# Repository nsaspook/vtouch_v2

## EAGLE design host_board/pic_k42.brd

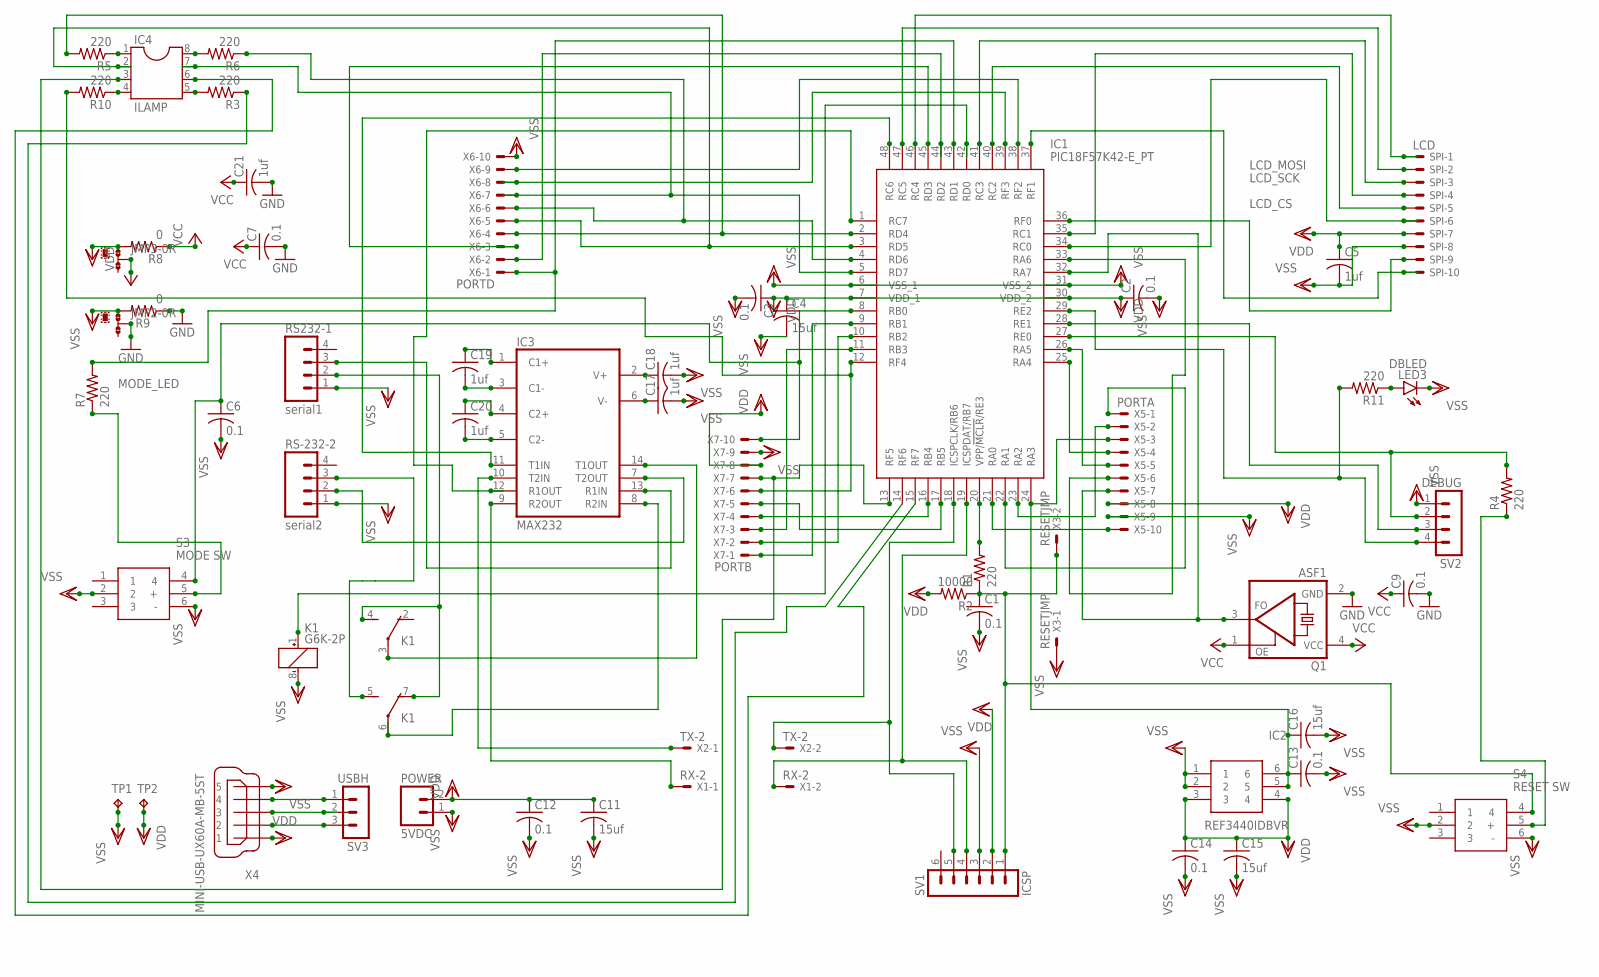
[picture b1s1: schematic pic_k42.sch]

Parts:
C1, C2, C3, C6, C7, C9, C12, C13, C14: 0.1; C1206
C4, C11, C15, C16: 15uf; C1206
C5, C17, C18, C19, C20, C21: 1uf; C0805
IC1: PIC18F57K42-E_PT; QFP50P900X900X120-48N
IC2: REF3440IDBVR; SOP95P280X145-6N
IC3: MAX232; DIL16
IC4: ILAMP; SOCKET-08
JMP2, JMP3: 0R-JUMPA; A0R-JMP
K1: G6K-2P
LED3: DBLED; CHIPLED_1206
POWER: 5VDC; 02P
Q1: ASF1; ASF
R1, R3, R4, R5, R6, R7, R10, R11: 220; R1206
R2: 10000; R1206
R8, R9: 0; R1206
RS232-1: serial1; 04P
RS-232-2: serial2; 04P
S3: MODE SW; B3W-9_1-LED
S4: RESET SW; B3W-9_1-LED
SPI: LCD; 22-23-2101
SV1: ICSP; MA06-1
SV2: DEBUG; MA04-1
SV3: USBH; MA03-1
TP1, TP2: TPB1,27; B1,27
X1: RX-2; 332-02
X2: TX-2; 332-02
X3: RESETJMP; 332-02
X4: MINI-USB-UX60A-MB-5ST; UX60A-MB-5ST
X5: PORTA; 22-23-2101
X6: PORTD; 22-23-2101
X7: PORTB; 22-23-2101

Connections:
GND: C7.2, C9.2, C21.2, IC3.15 (GND), JMP2.2, Q1.2 (GND), R9.1
LCD_CS: IC1.40 (RC2), SPI.5
LCD_MOSI: IC1.47 (RC5), SPI.2
LCD_SCK: IC1.41 (RC3), SPI.3
MODE_LED: IC1.43 (RD1), R7.2, X6.1
unnamed: C1.1, R1.1, R2.1, S4.4, SV1.1, X3.2
unnamed: IC1.20 (VPP/!MCLR!/RE3), R1.2
unnamed: IC4.1, R5.1
unnamed: IC1.32 (RA7), Q1.3 (FO), X5.7
unnamed: C17.1, IC3.6 (V-)
unnamed: IC1.19 (ICSPDAT/RB7), SV1.4, X1.2
unnamed: IC1.18 (ICSPCLK/RB6), SV1.5, X2.2
unnamed: C13.1, C16.1, IC1.24 (RA3), IC2.5, IC2.6, X5.3
unnamed: C18.1, IC3.2 (V+)
unnamed: C19.1, IC3.1 (C1+)
unnamed: C20.1, IC3.4 (C2+)
unnamed: C20.2, IC3.5 (C2-)
unnamed: C19.2, IC3.3 (C1-)
unnamed: K1.4 (S), K1.7 (O), RS232-1.2
unnamed: IC3.7 (T2OUT), RS-232-2.2
unnamed: IC3.13 (R1IN), RS232-1.3
unnamed: IC4.8, R6.2
unnamed: IC1.1 (RC7), IC3.12 (R1OUT)
unnamed: IC3.9 (R2OUT), X1.1
unnamed: IC1.48 (RC6), IC3.11 (T1IN)
unnamed: R4.1, S4.5 (+)
unnamed: IC3.10 (T2IN), X2.1
unnamed: IC1.27 (RE0), R4.2, SV2.2
unnamed: IC1.28 (RE1), SV2.3
unnamed: IC1.29 (RE2), R11.2, SV2.4
unnamed: IC3.14 (T1OUT), K1.3
unnamed: IC3.8 (R2IN), K1.6
unnamed: IC1.42 (RD0), K1.1 (+)
unnamed: IC1.46 (RC4), SPI.1
unnamed: IC1.35 (RC1), SPI.4
unnamed: IC1.34 (RC0), SPI.6
unnamed: IC1.26 (RA5), X5.5
unnamed: IC1.25 (RA4), X5.4
unnamed: IC1.23 (RA2), X5.2
unnamed: IC1.22 (RA1), X5.1
unnamed: IC1.21 (RA0), X5.10
unnamed: IC1.33 (RA6), X5.6
unnamed: IC1.36 (RF0), SPI.9
unnamed: IC1.37 (RF1), SPI.10
unnamed: C6.1, IC1.8 (RB0), S3.4, X7.10
unnamed: IC1.44 (RD2), X6.2
unnamed: IC1.45 (RD3), X6.3
unnamed: IC1.2 (RD4), R5.2, X6.4
unnamed: IC1.3 (RD5), IC4.2, X6.5
unnamed: IC1.4 (RD6), R6.1, X6.6
unnamed: IC1.5 (RD7), IC4.7, X6.7
unnamed: IC1.38 (RF2), X6.9
unnamed: IC1.39 (RF3), X6.8
unnamed: IC1.9 (RB1), X7.1
unnamed: IC1.10 (RB2), X7.2
unnamed: IC4.5, R3.2
unnamed: IC1.16 (RB4), X7.4
unnamed: IC1.17 (RB5), X7.5
unnamed: IC1.12 (RF4), R10.2, X7.6
unnamed: IC1.13 (RF5), IC4.3, X7.7
unnamed: IC1.15 (RF7), IC4.6
unnamed: IC1.14 (RF6), R3.1
unnamed: K1.5 (S), RS-232-2.3
unnamed: IC4.4, R10.1
unnamed: R7.1, S3.5 (+)
unnamed: LED3.A, R11.1
unnamed: IC1.11 (RB3), X7.3
unnamed: SV3.1, X4.4
unnamed: SV3.2, X4.3
unnamed: SV3.3, X4.2
VCC: C7.1, C9.1, C21.1, IC3.16 (VCC), JMP3.2, Q1.1 (OE), Q1.4 (VCC), R8.1
VDD: C2.1, C3.1, C4.1, C5.1, C11.1, C12.1, C14.1, C15.1, IC1.7 (VDD_1), IC1.30 (VDD_2), IC2.3, IC2.4, JMP3.1, POWER.2, R2.2, R8.2, SPI.7, SV1.2, TP2.TP, X4.1, X5.8, X7.8
VSS: C1.2, C2.2, C3.2, C4.2, C5.2, C6.2, C11.2, C12.2, C13.2, C14.2, C15.2, C16.2, C17.2, C18.2, IC1.6 (VSS_1), IC1.31 (VSS_2), IC2.1, IC2.2, JMP2.1, K1.8 (-), LED3.C, POWER.1, R9.2, RS232-1.1, RS-232-2.1, S3.2, S3.6 (-), S4.2, S4.6 (-), SPI.8, SV1.3, SV2.1, TP1.TP, X3.1, X4.5, X5.9, X6.10, X7.9

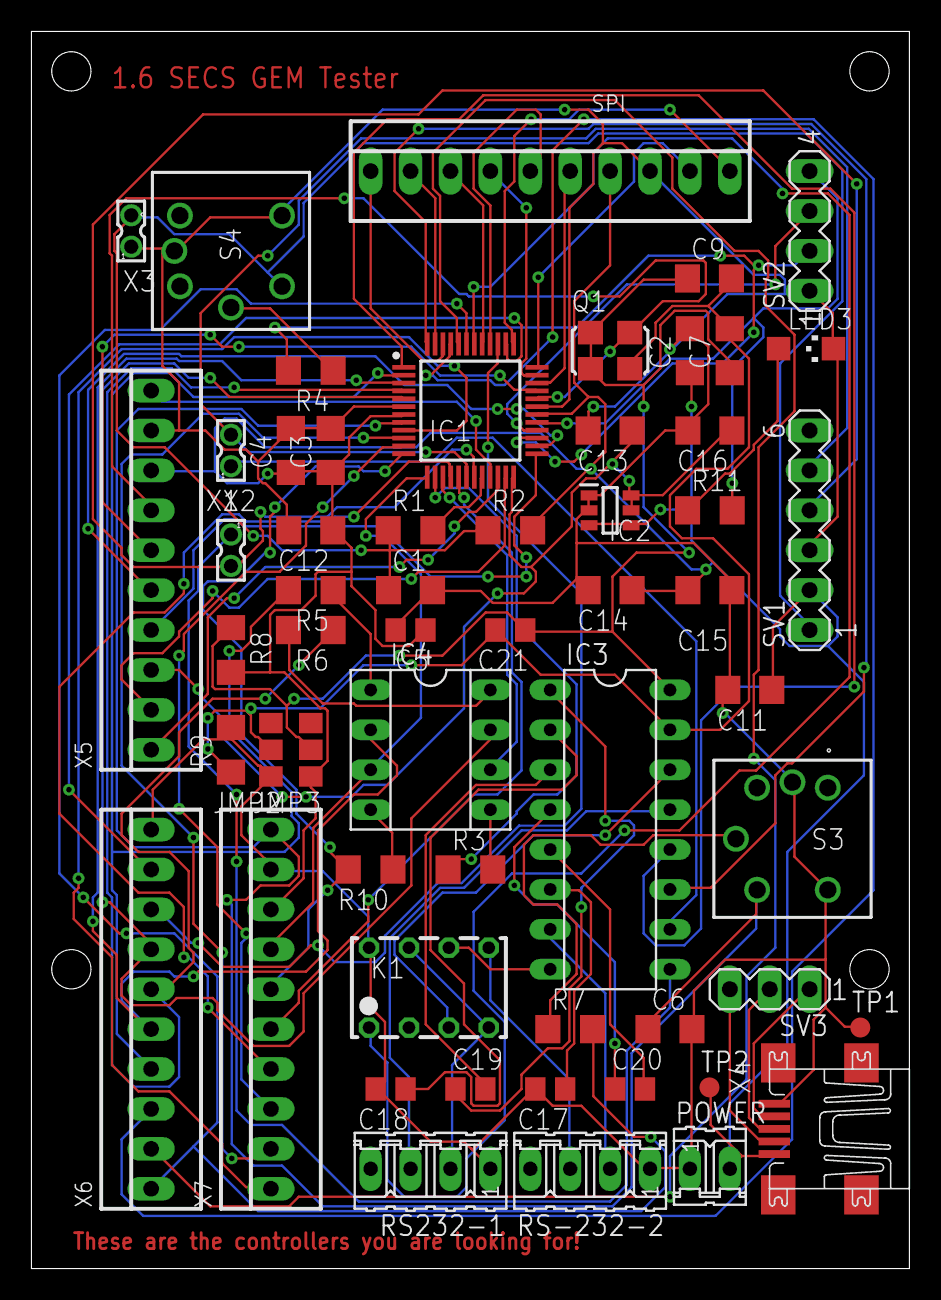
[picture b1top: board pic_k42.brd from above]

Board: 2 copper layers, 55.9 x 78.7 mm, 57 parts (0 on the bottom side), 73 nets.

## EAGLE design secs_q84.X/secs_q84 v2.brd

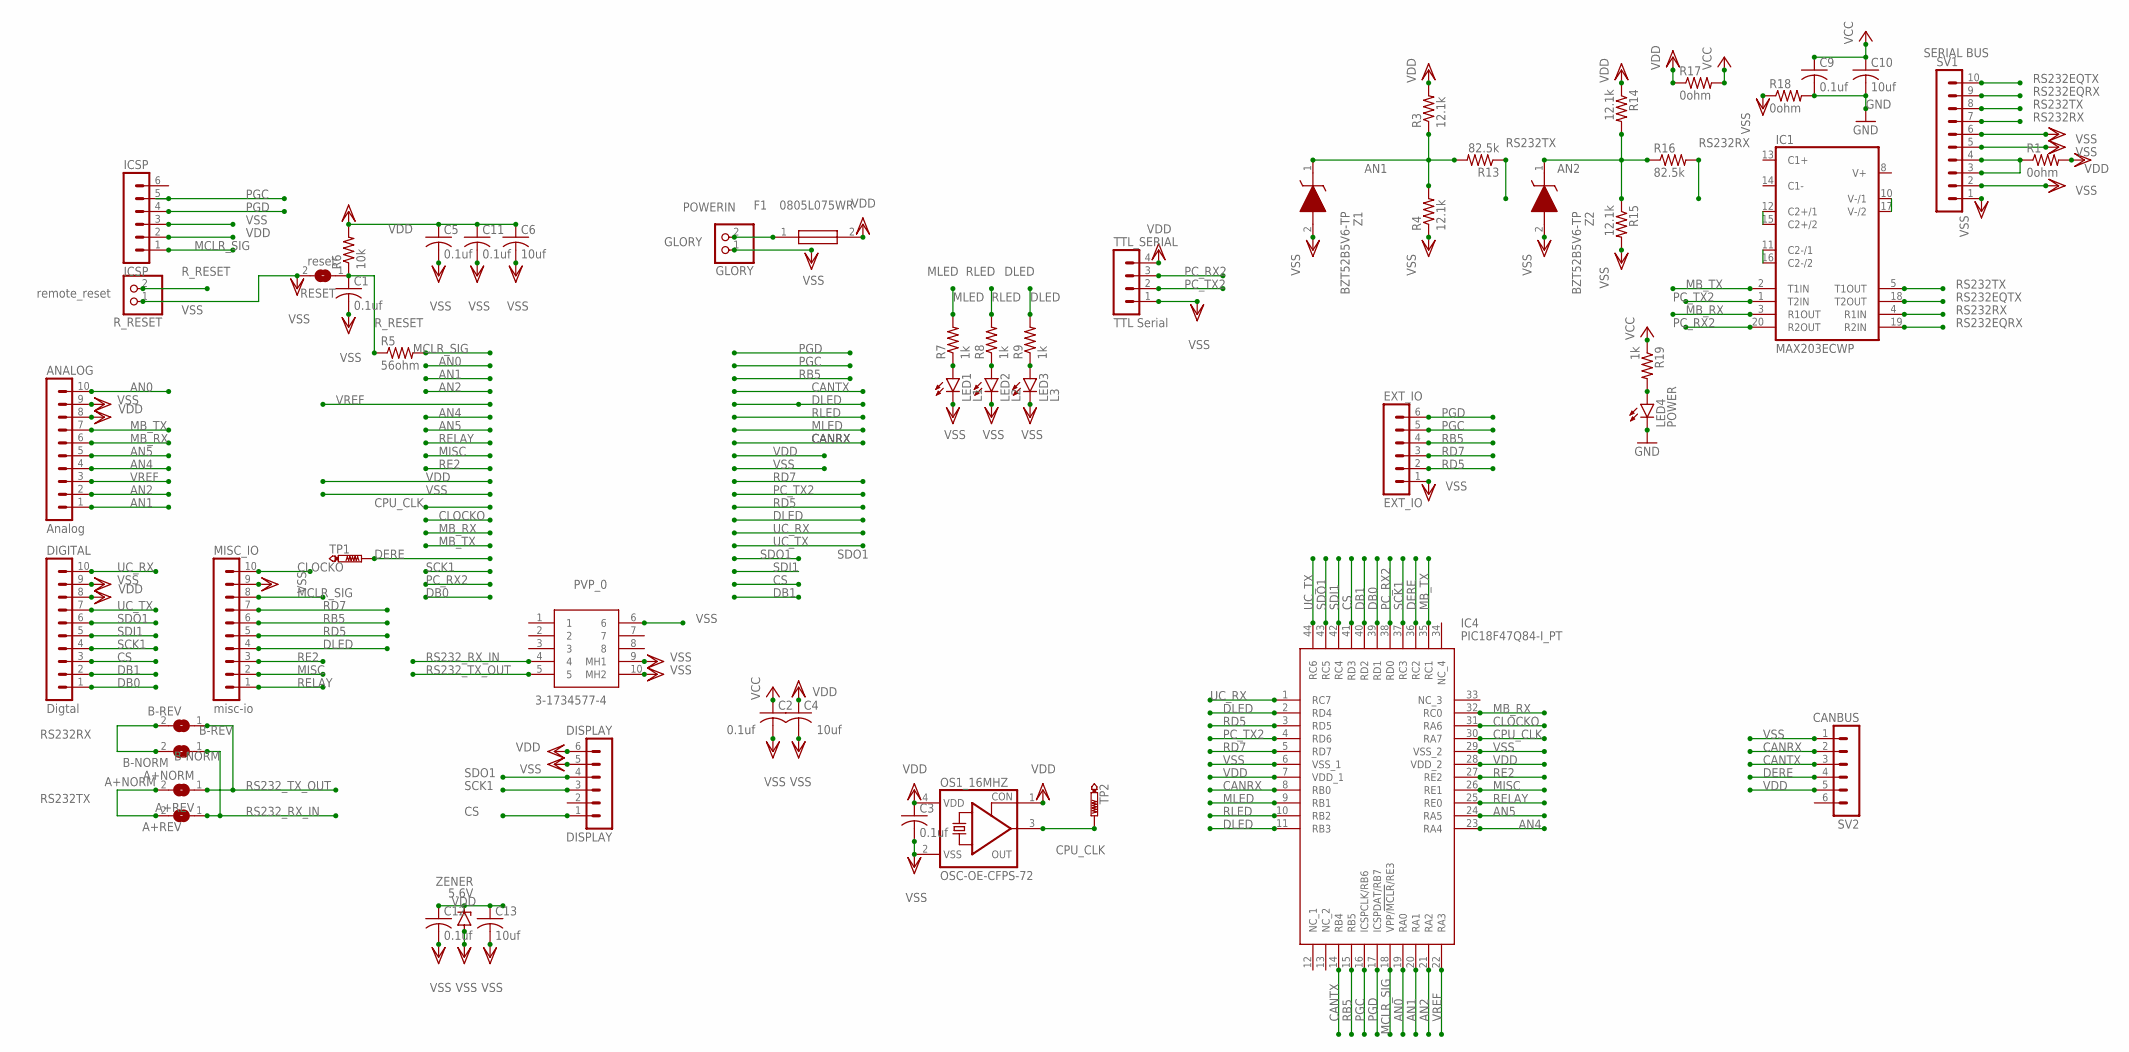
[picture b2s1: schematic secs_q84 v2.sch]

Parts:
A+NORM: A+NORM; SJ
A+REV: A+REV; SJ
ANALOG: Analog; MA10-1
B-NORM: B-NORM; SJ
B-REV: B-REV; SJ
C1, C2, C3, C5, C9, C11, C12: 0.1uf; C0805
C4, C6, C10, C13: 10uf; C0805
DIGITAL: Digtal; MA10-1
DISPLAY: DISPLAY; MA06-1
EXT_IO: EXT_IO; MA06-1
F1: 0805L075WR; FUSC2114X125N
GLORY: GLORY; 1X02
IC1: MAX203ECWP; SO20L
IC4: PIC18F47Q84-I_PT; QFP80P1200X1200X120-44N
ICSP: ICSP; MA06-1
LED1: L1; CHIPLED_0805
LED2: L2; CHIPLED_0805
LED3: L3; CHIPLED_0805
LED4: POWER; CHIP-LED0603
MISC_IO: misc-io; MA10-1
OS1_16MHZ: OSC-OE-CFPS-72; 7.2X5.2-4-PAD
PVP_0: 3-1734577-4; 317345774
R1, R17, R18: 0ohm; R0805
R3, R4, R14, R15: 12.1k; R0805
R5: 56ohm; R0805
R6: 10k; R0805
R7, R8, R9, R19: 1k; R0805
R13, R16: 82.5k; R0805
RESET: reset; SJ
R_RESET: remote_reset; 1X02
SV1: SERIAL BUS; MA10-1
SV2: CANBUS; MA06-1
TP1, TP2: PTR1PAD1-13; P1-13
TTL_SERIAL: TTL Serial; MA04-1
Z1, Z2: BZT52B5V6-TP; SOD3716X135N
ZENER: 5.6V; SMB

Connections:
AN0: ANALOG.10, IC4.19 (RA0)
AN1: ANALOG.1, IC4.20 (RA1), R3.1, R4.2, R13.2, Z1.1 (K)
AN2: ANALOG.2, IC4.21 (RA2), R14.2, R15.1, R16.1, Z2.1 (K)
AN4: ANALOG.4, IC4.23 (RA4)
AN5: ANALOG.5, IC4.24 (RA5)
CANRX: IC4.8 (RB0), SV2.2
CANTX: IC4.14 (RB4), SV2.3
CLOCKO: IC4.31 (RA6), MISC_IO.10
CPU_CLK: IC4.30 (RA7), OS1_16MHZ.3 (OUT), TP2.TP
CS: DIGITAL.3, DISPLAY.1, IC4.41 (RD3)
DB0: DIGITAL.1, IC4.39 (RD1)
DB1: DIGITAL.2, IC4.40 (RD2)
DERE: IC4.36 (RC2), SV2.4, TP1.TP
DLED: IC4.2 (RD4), IC4.11 (RB3), MISC_IO.4, R9.2
DPOWER: R1.1, SV1.3, SV1.4
GND: C9.2, C10.2, IC1.6 (GND), IC1.9 (GND), LED4.C, R18.2
MB_RX: ANALOG.6, IC1.3 (R1OUT), IC4.32 (RC0)
MB_TX: ANALOG.7, IC1.2 (T1IN), IC4.35 (RC1)
MCLR_SIG: IC4.18 (VPP/!MCLR!/RE3), ICSP.1, MISC_IO.8, R5.2
MISC: IC4.26 (RE1), MISC_IO.2
MLED: IC4.9 (RB1), R7.2
unnamed: IC1.10 (V-/1), IC1.17 (V-/2)
unnamed: IC1.12 (C2+/1), IC1.15 (C2+/2)
unnamed: LED4.A, R19.2
unnamed: LED1.A, R7.1
unnamed: LED2.A, R8.1
unnamed: LED3.A, R9.1
unnamed: IC1.11 (C2-/1), IC1.16 (C2-/2)
PC_RX2: IC1.20 (R2OUT), IC4.38 (RD0), TTL_SERIAL.3
PC_TX2: IC1.1 (T2IN), IC4.4 (RD6), TTL_SERIAL.2
PGC: EXT_IO.5, IC4.16 (ICSPCLK/RB6), ICSP.5
PGD: EXT_IO.6, IC4.17 (ICSPDAT/RB7), ICSP.4
POWERIN: F1.1, GLORY.2
RB5: EXT_IO.4, IC4.15 (RB5), MISC_IO.6
RD5: EXT_IO.2, IC4.3 (RD5), MISC_IO.5
RD7: EXT_IO.3, IC4.5 (RD7), MISC_IO.7
RE2: IC4.27 (RE2), MISC_IO.3
RELAY: IC4.25 (RE0), MISC_IO.1
RLED: IC4.10 (RB2), R8.2
RS232EQRX: IC1.19 (R2IN), SV1.9
RS232EQTX: IC1.18 (T2OUT), SV1.10
RS232RX: B-NORM.2, B-REV.2, IC1.4 (R1IN), R16.2, SV1.7
RS232TX: A+NORM.2, A+REV.2, IC1.5 (T1OUT), R13.1, SV1.8
RS232_RX_IN: A+REV.1, B-NORM.1, PVP_0.4
RS232_TX_OUT: A+NORM.1, B-REV.1, PVP_0.5
R_RESET: C1.1, R5.1, R6.1, RESET.1, R_RESET.2
SCK1: DIGITAL.4, DISPLAY.3, IC4.37 (RC3)
SDI1: DIGITAL.5, IC4.42 (RC4)
SDO1: DIGITAL.6, DISPLAY.4, IC4.43 (RC5)
UC_RX: DIGITAL.10, IC4.1 (RC7)
UC_TX: DIGITAL.7, IC4.44 (RC6)
VCC: C2.1, C9.1, C10.1, IC1.7 (VCC), R17.2, R19.1
VDD: ANALOG.8, C3.1, C4.1, C5.1, C6.1, C11.1, C12.1, C13.1, DIGITAL.8, DISPLAY.6, F1.2, IC4.7 (VDD_1), IC4.28 (VDD_2), ICSP.2, OS1_16MHZ.1 (CON), OS1_16MHZ.4 (VDD), R1.2, R3.2, R6.2, R14.1, R17.1, SV2.5, TTL_SERIAL.4, ZENER.C
VREF: ANALOG.3, IC4.22 (RA3)
VSS: ANALOG.9, C1.2, C2.2, C3.2, C4.2, C5.2, C6.2, C11.2, C12.2, C13.2, DIGITAL.9, DISPLAY.5, EXT_IO.1, GLORY.1, IC4.6 (VSS_1), IC4.29 (VSS_2), ICSP.3, LED1.C, LED2.C, LED3.C, MISC_IO.9, OS1_16MHZ.2 (VSS), PVP_0.6, PVP_0.9 (MH1), PVP_0.10 (MH2), R4.1, R15.2, R18.1, RESET.2, R_RESET.1, SV1.1, SV1.2, SV1.5, SV1.6, SV2.1, TTL_SERIAL.1, Z1.2 (A), Z2.2 (A), ZENER.A

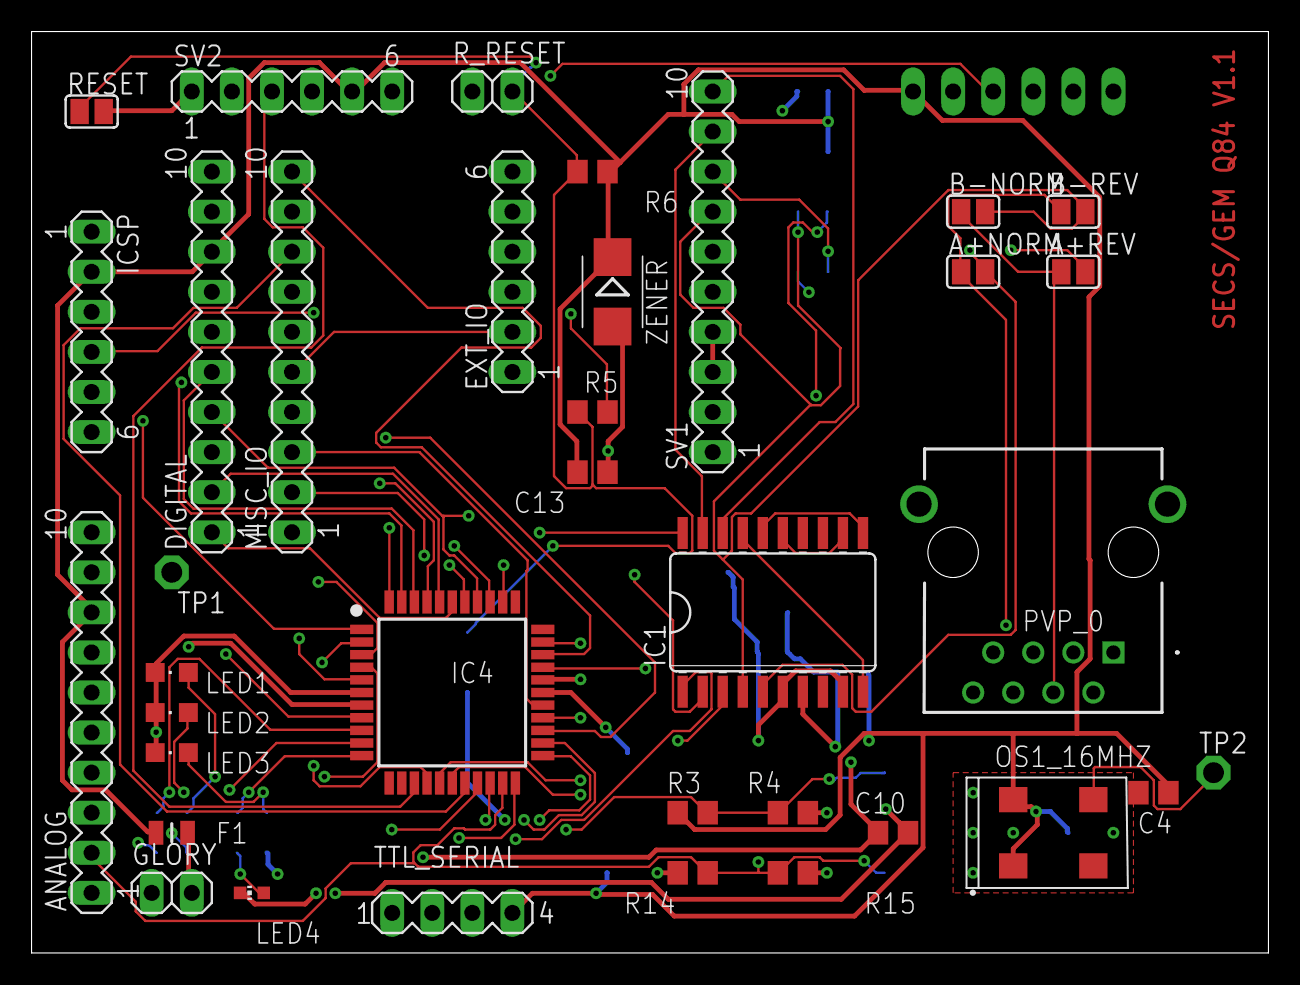
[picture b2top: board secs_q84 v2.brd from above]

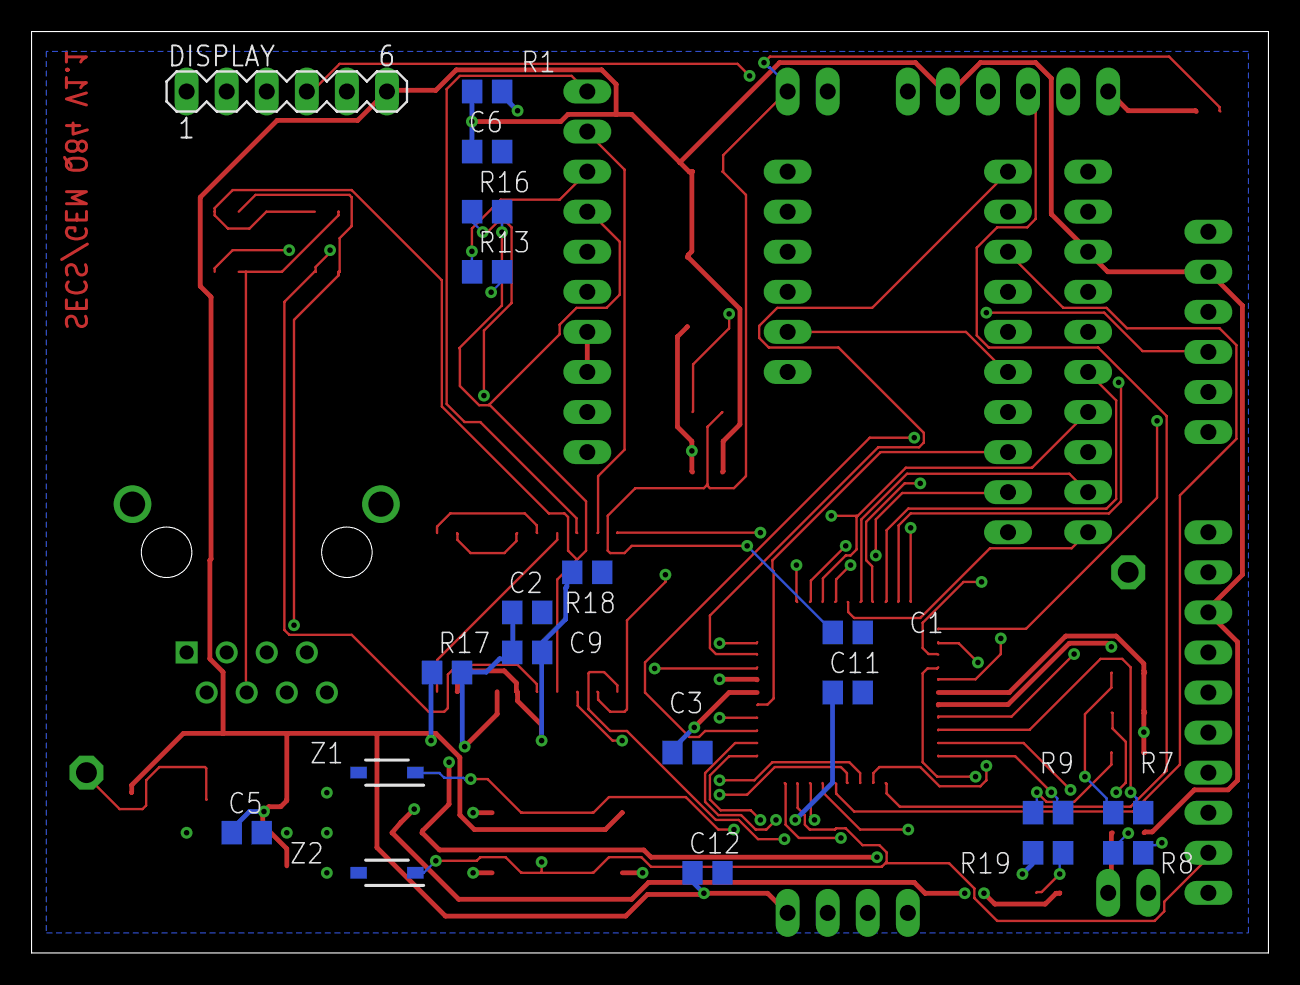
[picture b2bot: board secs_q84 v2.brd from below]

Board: 4 copper layers, 78.4 x 58.4 mm, 56 parts (20 on the bottom side), 55 nets.

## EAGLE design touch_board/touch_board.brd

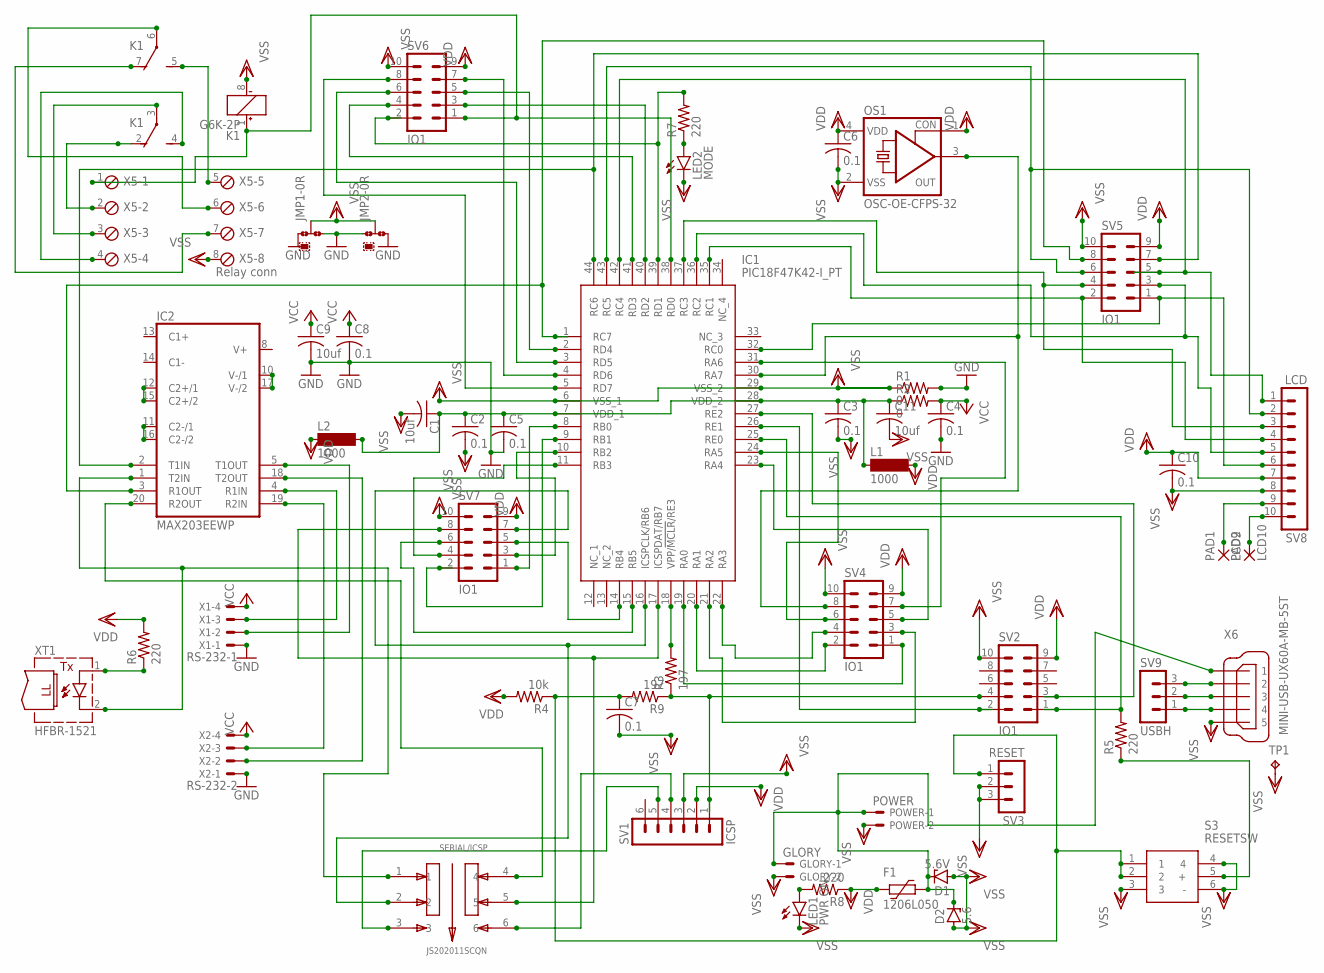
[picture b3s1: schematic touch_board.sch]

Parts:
C1, C9, C11: 10uf; C0805
C2, C3, C4, C5, C6, C7, C8, C10: 0.1; C0805
D1: 5.6V; ZDIO-7.5
D2: 5.6; SMB
F1: 1206L050; 1206L
GLORY: GLORY; 22-23-2021
IC1: PIC18F47K42-I_PT; QFP80P1200X1200X120-44N
IC2: MAX203EEWP; SO20L
JMP1, JMP2: 0R-JUMPA; A0R-JMP
K1: G6K-2P
L1, L2: 1000; SM-1206
LED1: PWR ON; CHIPLED_1206
LED2: MODE; CHIPLED_1206
OS1: OSC-OE-CFPS-32; 7.2X5.2-4-PAD
PAD1: LCD9; SMD1,27-2,54
PAD2: LCD10; SMD1,27-2,54
POWER: POWER; 22-23-2021
R1, R2: 0; R0805
R3, R9: 197; R0805
R4: 10k; R0805
R5, R6, R7, R8: 220; R0805
S3: RESETSW; B3W-9_1-LED
SERIAL/ICSP: JS202011SCQN; SW_JS202011SCQN
SV1: ICSP; MA06-1
SV2, SV4, SV5, SV6, SV7: IO1; MA05-2
SV3: RESET; MA03-1
SV8: LCD; MA10-1
SV9: USBH; MA03-1
TP1: TPB1,27; B1,27
X1: RS-232-1; 22-23-2041
X2: RS-232-2; 22-23-2041
X5: Relay conn; 8POL254
X6: MINI-USB-UX60A-MB-5ST; UX60A-MB-5ST
XT1: HFBR-1521; HFBR-15X3

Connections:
GND: C4.2, C5.2, C8.2, C9.2, IC2.6 (GND), IC2.9 (GND), JMP1.1, JMP1.3, JMP2.1, JMP2.3, R1.2, X1.1, X2.1
unnamed: IC1.30 (RA7), OS1.3 (OUT), SV4.8
unnamed: R3.1, R9.1, SV1.1, SV2.4
unnamed: IC1.18 (VPP/!MCLR!/RE3), R3.2
unnamed: IC1.25 (RE0), R5.2, SV2.1
unnamed: IC1.26 (RE1), SV2.2
unnamed: IC1.17 (ICSPDAT/RB7), SERIAL/ICSP.5, SV7.8
unnamed: IC1.16 (ICSPCLK/RB6), SERIAL/ICSP.2, SV7.7
unnamed: IC1.27 (RE2), SV2.3
unnamed: R5.1, S3.5 (+)
unnamed: IC1.39 (RD1), R7.2, SV6.2
unnamed: LED2.A, R7.1
unnamed: IC2.11 (C2-/1), IC2.16 (C2-/2)
unnamed: IC2.10 (V-/1), IC2.17 (V-/2)
unnamed: IC2.12 (C2+/1), IC2.15 (C2+/2)
unnamed: IC2.5 (T1OUT), X1.2
unnamed: IC2.18 (T2OUT), X2.2
unnamed: IC2.4 (R1IN), X1.3
unnamed: IC2.19 (R2IN), X2.3
unnamed: IC1.44 (RC6), IC2.2 (T1IN), SV5.7
unnamed: IC2.1 (T2IN), SERIAL/ICSP.1, XT1.2 (C)
unnamed: IC1.1 (RC7), IC2.3 (R1OUT), SV5.8
unnamed: IC2.20 (R2OUT), SERIAL/ICSP.4
unnamed: SERIAL/ICSP.6, SV1.4
unnamed: R6.1, XT1.1 (A)
unnamed: IC1.19 (RA0), SV4.1
unnamed: IC1.20 (RA1), SV4.2
unnamed: IC1.21 (RA2), SV4.3
unnamed: IC1.22 (RA3), SV4.4
unnamed: IC1.23 (RA4), SV4.5
unnamed: IC1.31 (RA6), SV4.7
unnamed: IC1.24 (RA5), SV4.6
unnamed: IC1.32 (RC0), SV5.1, SV8.6
unnamed: IC1.35 (RC1), SV5.2, SV8.4
unnamed: IC1.36 (RC2), SV5.3, SV8.5
unnamed: IC1.37 (RC3), SV5.4, SV8.3
unnamed: LED1.A, R8.2
unnamed: IC1.43 (RC5), SV5.6, SV8.2
unnamed: K1.2 (O), X5.2
unnamed: IC1.40 (RD2), SV6.3
unnamed: IC1.41 (RD3), SV6.4
unnamed: IC1.2 (RD4), SV6.5
unnamed: IC1.3 (RD5), SV6.6
unnamed: IC1.4 (RD6), SV6.7
unnamed: IC1.5 (RD7), SV6.8
unnamed: IC1.8 (RB0), SV7.1
unnamed: IC1.9 (RB1), SV7.2
unnamed: IC1.10 (RB2), SV7.3
unnamed: IC1.11 (RB3), SV7.4
unnamed: IC1.14 (RB4), SV7.5
unnamed: IC1.15 (RB5), SV7.6
unnamed: IC1.38 (RD0), K1.1 (+), SV6.1, X5.1
unnamed: K1.3, X5.3
unnamed: K1.4 (S), X5.4
unnamed: K1.5 (S), X5.5
unnamed: K1.6, X5.6
unnamed: K1.7 (O), X5.7
unnamed: C1.1, C2.1, C3.1, C5.1, C11.1, IC1.7 (VDD_1), IC1.28 (VDD_2), L1.1, L2.2, R2.1
unnamed: SV9.3, X6.2
unnamed: D1.C, D2.C, F1.1, GLORY.1, POWER.1, X6.1
unnamed: SV9.2, X6.3
unnamed: C7.1, R4.1, R9.2, S3.1, S3.2, SV3.1
unnamed: IC1.42 (RC4), SV5.5, SV8.1
unnamed: SV9.1, X6.4
unnamed: SERIAL/ICSP.3, SV1.5
unnamed: PAD1.1, SV8.9
unnamed: PAD2.1, SV8.10
VCC: C4.1, C8.1, C9.1, IC2.7 (VCC), R2.2, X1.4, X2.4
VDD: C6.1, C10.1, F1.2, L1.2, L2.1, OS1.1 (CON), OS1.4 (VDD), R4.2, R6.2, R8.1, SV1.2, SV2.9, SV4.9, SV5.9, SV6.9, SV7.9, SV8.7
VSS: C1.2, C2.2, C3.2, C6.2, C7.2, C10.2, C11.2, D1.A, D2.A, GLORY.2, IC1.6 (VSS_1), IC1.29 (VSS_2), JMP1.2, JMP2.2, K1.8 (-), LED1.C, LED2.C, OS1.2 (VSS), POWER.2, R1.1, S3.3, S3.4, S3.6 (-), SV1.3, SV2.10, SV3.2, SV3.3, SV4.10, SV5.10, SV6.10, SV7.10, SV8.8, TP1.TP, X5.8, X6.5

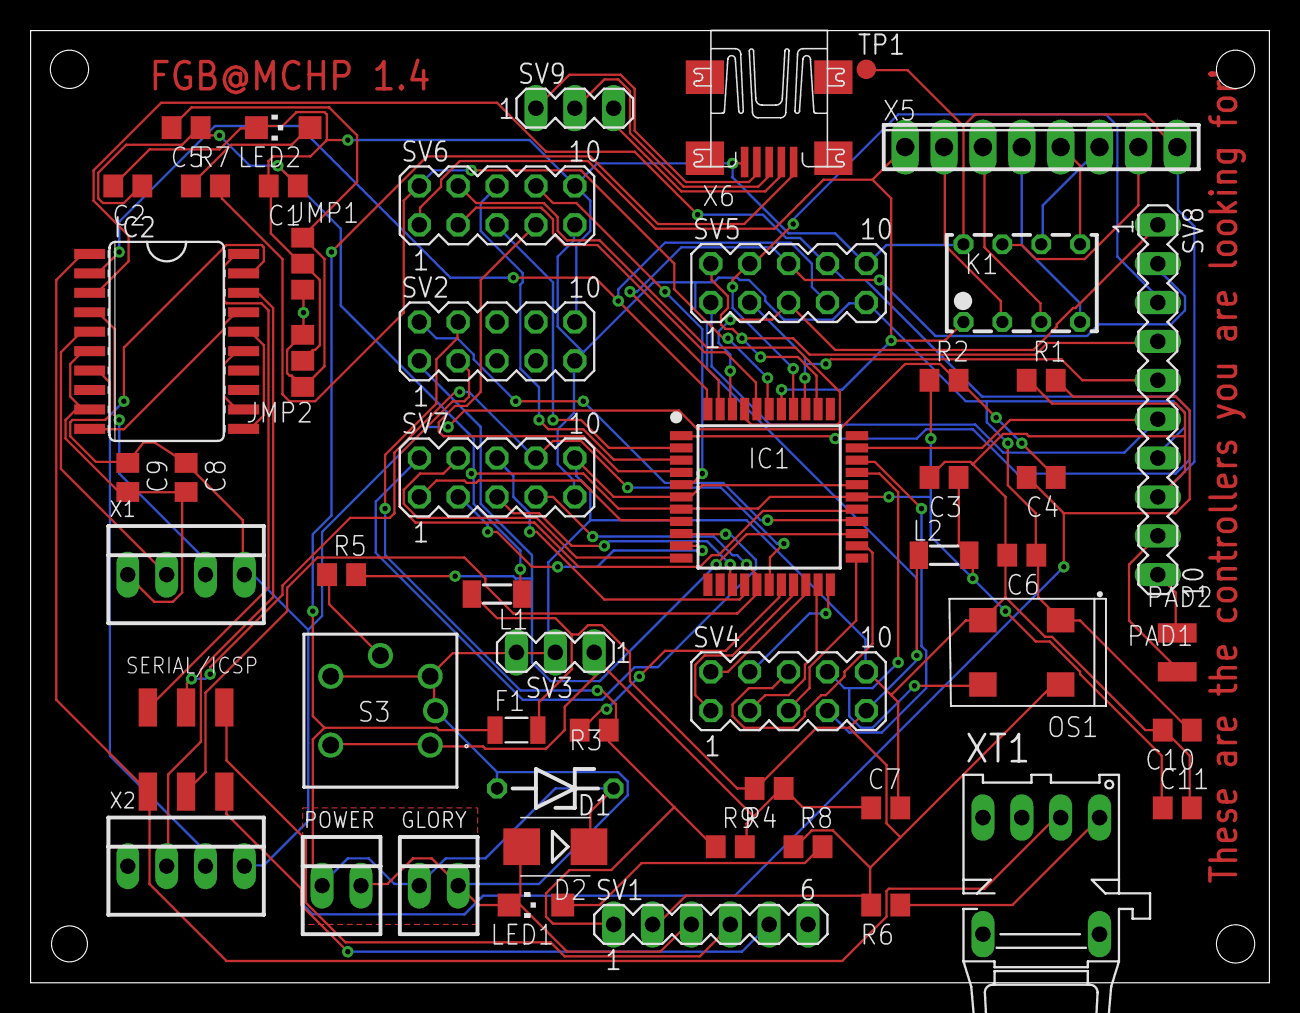
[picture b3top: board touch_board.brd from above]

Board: 2 copper layers, 81.0 x 62.2 mm, 54 parts (0 on the bottom side), 70 nets.

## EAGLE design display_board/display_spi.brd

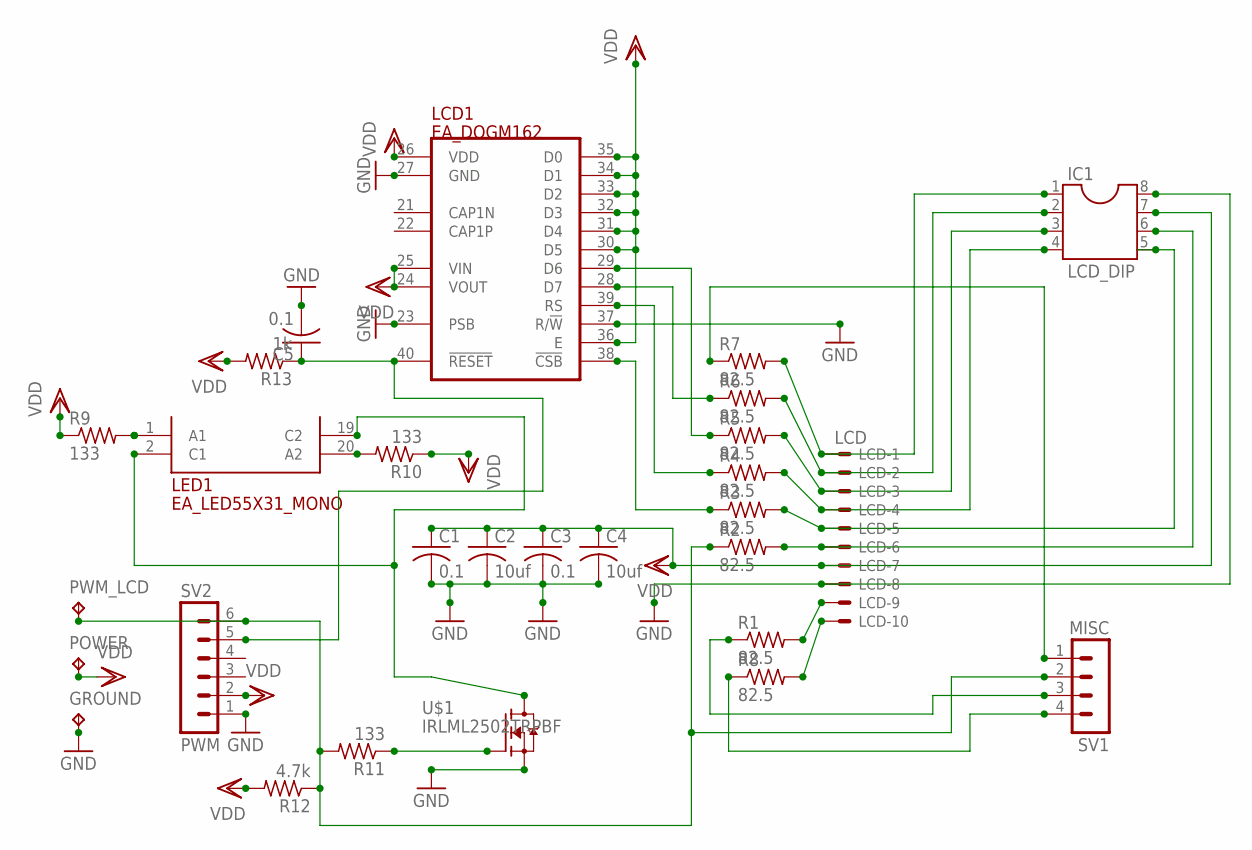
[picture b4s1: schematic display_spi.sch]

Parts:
C1, C3, C5: 0.1; C1206
C2, C4: 10uf; C1206
GROUND: TPB1,27; B1,27
IC1: LCD_DIP; SOCKET-08
LCD: LCD; 22-23-2101
LCD1: EA_DOGM162; EA_DOGM
LED1: EA_LED55X31_MONO; EA_LED55X31
POWER: TPB1,27; B1,27
PWM_LCD: PWM; B1,27
R1, R2, R3, R4, R5, R6, R7, R8: 82.5; R0805
R9, R10, R11: 133; R1206
R12: 4.7k; R1206
R13: 1k; R1206
SV1: MISC; MA04-1
SV2: PWM; MA06-1
U$1: IRLML2502TRPBF; SOT23

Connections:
GND: C1.2, C2.2, C3.2, C4.2, C5.2, GROUND.TP, IC1.8, LCD.8, LCD1.23 (PSB), LCD1.27 (GND), LCD1.37 (R/!W!), SV2.1, U$1.2 (S)
unnamed: IC1.1, LCD.1, R7.2
unnamed: IC1.2, LCD.2, R6.2
unnamed: IC1.3, LCD.3, R5.2
unnamed: IC1.4, LCD.4, R4.2
unnamed: IC1.5, LCD.5, R3.2
unnamed: IC1.6, LCD.6, R2.2
unnamed: LCD.9, R1.2
unnamed: LCD.10, R8.2
unnamed: LCD1.28 (D7), R6.1
unnamed: LCD1.29 (D6), R5.1
unnamed: LCD1.39 (RS), R4.1
unnamed: LCD1.38 (!CSB!), R3.1
unnamed: R7.1, SV1.1
unnamed: PWM_LCD.TP, R2.1, R11.2, R12.1, SV1.2, SV2.6
unnamed: R1.1, SV1.3
unnamed: R8.1, SV1.4
unnamed: LED1.1 (A1), R9.2
unnamed: LED1.20 (A2), R10.2
unnamed: LED1.2 (C1), LED1.19 (C2), U$1.3 (D)
unnamed: C5.1, LCD1.40 (!RESET!), R13.1, SV2.5
unnamed: R11.1, U$1.1 (G)
VDD: C1.1, C2.1, C3.1, C4.1, IC1.7, LCD.7, LCD1.24 (VOUT), LCD1.25 (VIN), LCD1.26 (VDD), LCD1.30 (D5), LCD1.31 (D4), LCD1.32 (D3), LCD1.33 (D2), LCD1.34 (D1), LCD1.35 (D0), LCD1.36 (E), POWER.TP, R9.1, R10.1, R12.2, R13.2, SV2.2

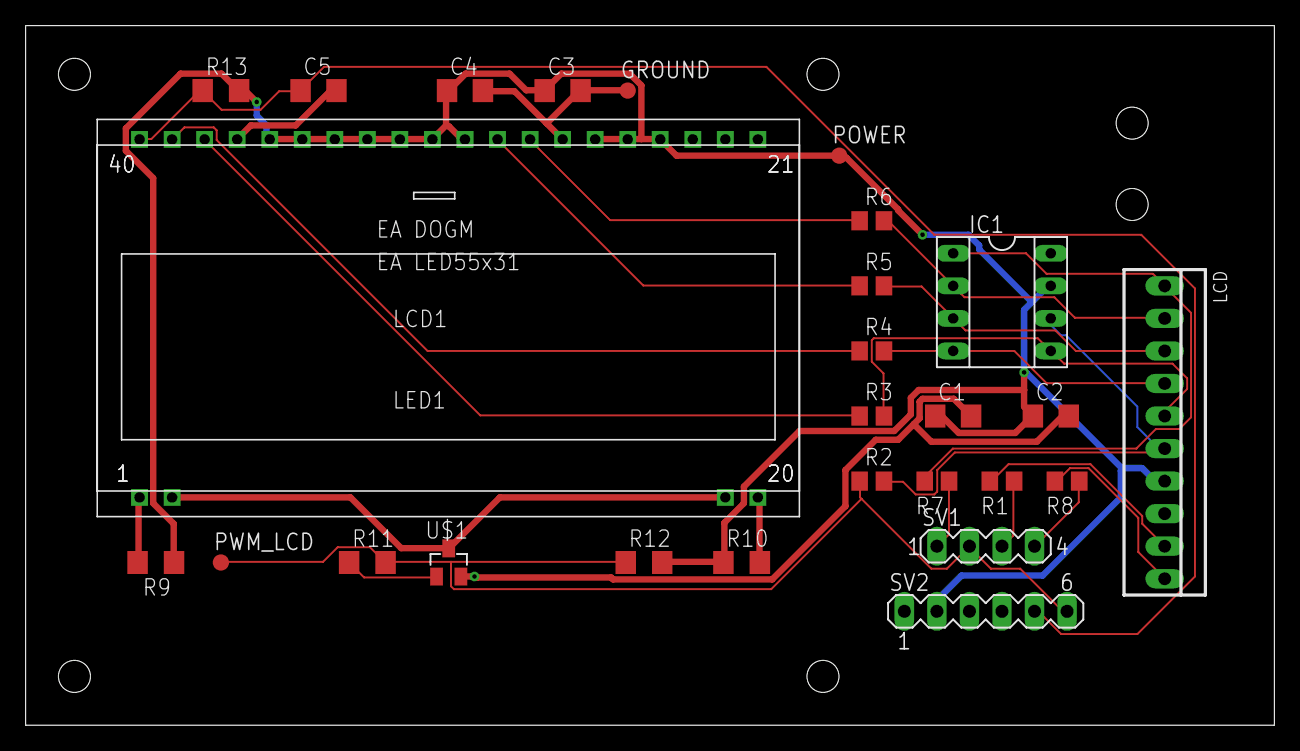
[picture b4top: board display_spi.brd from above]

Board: 2 copper layers, 97.5 x 54.6 mm, 28 parts (0 on the bottom side), 23 nets.
